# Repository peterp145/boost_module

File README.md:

# boost_module
op amp boost module for guitar. designed for use on a breadboard or in an enclosure.

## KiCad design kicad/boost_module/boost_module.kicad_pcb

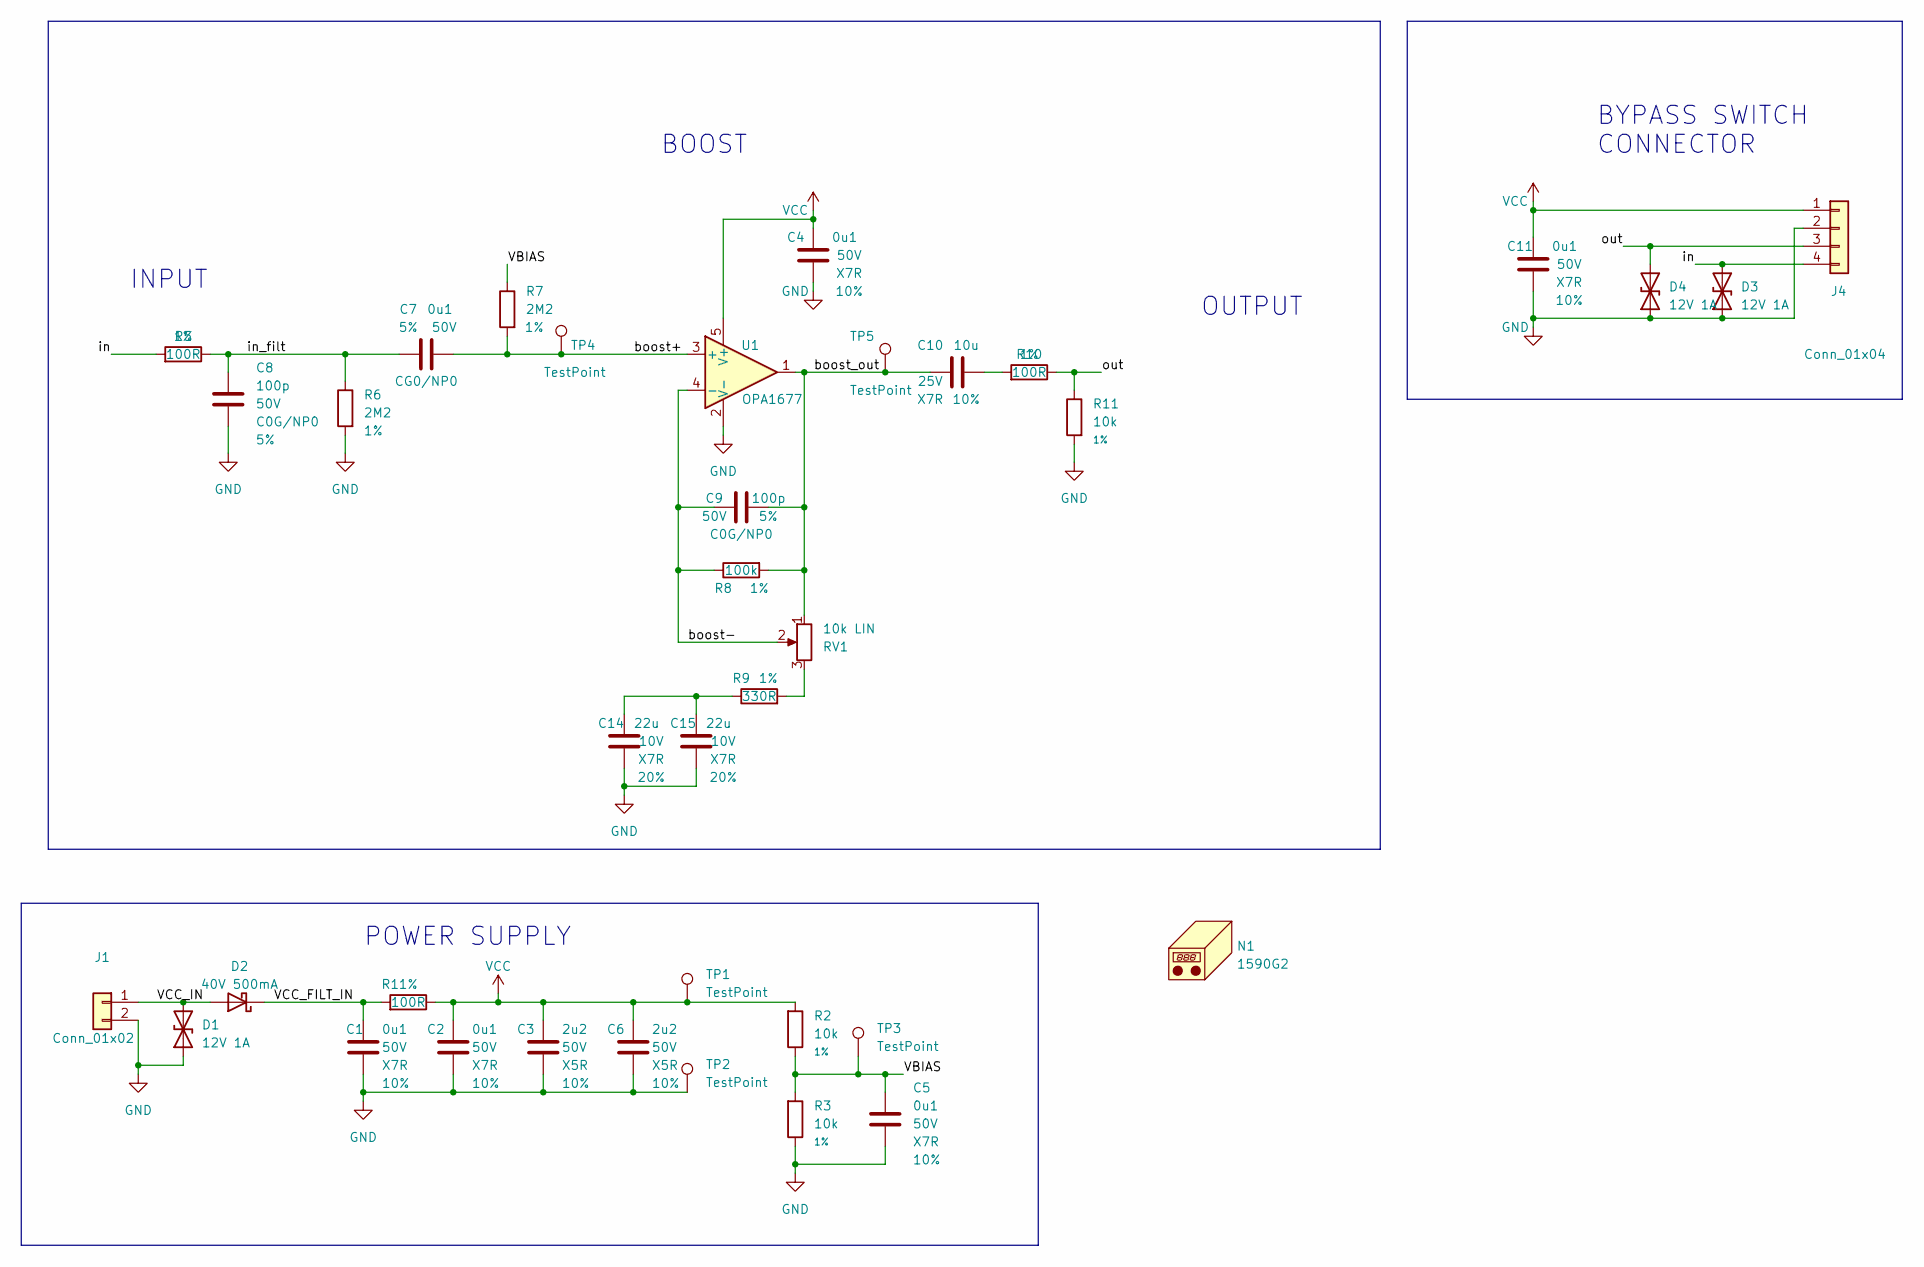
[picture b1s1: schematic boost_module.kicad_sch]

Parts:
C1, C2, C4, C5, C11: 0u1; C_0603_1608Metric; Voltage 50V; Tolerance 10%; MPN1 CL10B104KB8NNWC
C3, C6: 2u2; C_0603_1608Metric; Voltage 50V; Tolerance 10%; MPN1 UMK107BBJ225KA-T
C7: 0u1; C_1206_3216Metric; Voltage 50V; Tolerance 5%; MPN1 CGA5L2C0G1H104J160AA
C8, C9: 100p; C_0603_1608Metric; Voltage 50V; Tolerance 5%; MPN1 CC0603JRNPO9BN101
C10: 10u; C_1206_3216Metric; Voltage 25V; Tolerance 10%; MPN1 CL31B106KAHNNNE
C14, C15: 22u; C_1206_3216Metric; Voltage 10V; Tolerance 20%; mfg_pn CL32B226MOJNNNE
D1, D3, D4: 12V 1A; D_SOD-323; MPN1 PJGBLC12C_R1_00001
D2: 40V 500mA; D_SOD-323; MPN1 CMDSH05-4 TR PBFREE
J1: Conn_01x02; PinHeader_1x02_P2.54mm_Vertical
J4: Conn_01x04; PinSocket_1x04_P2.54mm_Vertical
N1: 1590G2; 1590G
R1, R5, R10: 100R; R_0603_1608Metric; Tolerance 1%; MPN1 RC0603FR-07100RL
R2, R3, R11: 10k; R_0603_1608Metric; Tolerance 1%; MPN1 RC0603FR-0710KL
R6, R7: 2M2; R_0603_1608Metric; Tolerance 1%; MPN1 RC0603FR-072M2L
R8: 100k; R_0603_1608Metric; Tolerance 1%; MPN1 RC0603FR-07100KL
R9: 330R; R_0603_1608Metric; Tolerance 1%; MPN1 RC0603FR-07330RL
RV1: 10k LIN; Pot_RD901F-40-00D_Single_Vertical; Tolerance xx%
TP1, TP2, TP3, TP4, TP5: TestPoint; TestPoint_Pad_D1.0mm
U1: OPA1677; TSOT-23-5; MPN1 OPA1677DBVR

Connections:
/VBIAS: C5.1, R2.2, R3.1, R7.2, TP3.1
/VCC_FILT_IN: C1.1, D2.1 (K), R1.1
/VCC_IN: D1.2 (A2), D2.2 (A), J1.1
/boost+: C7.2, R7.1, TP4.1, U1.3 (+)
/boost-: C9.1, R8.2, RV1.2, U1.4 (-)
/boost_out: C9.2, C10.1, R8.1, RV1.1, TP5.1, U1.1
/in: D3.2 (A2), J4.4, R5.1
/in_filt: C7.1, C8.2, R5.2, R6.2
/out: D4.2 (A2), J4.3, R10.2, R11.2
GND: C1.2, C2.2, C3.2, C4.2, C5.2, C6.2, C8.1, C11.2, C14.2, C15.2, D1.1 (A1), D3.1 (A1), D4.1 (A1), J1.2, J4.2, R3.2, R6.1, R11.1, TP2.1, U1.2 (V-)
unnamed: C10.2, R10.1
unnamed: C14.1, C15.1, R9.2
unnamed: R9.1, RV1.3
VCC: C2.1, C3.1, C4.1, C6.1, C11.1, J4.1, R1.2, R2.1, TP1.1, U1.5 (V+)

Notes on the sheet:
BYPASS SWITCH CONNECTOR
OUTPUT
INPUT
BOOST
POWER SUPPLY

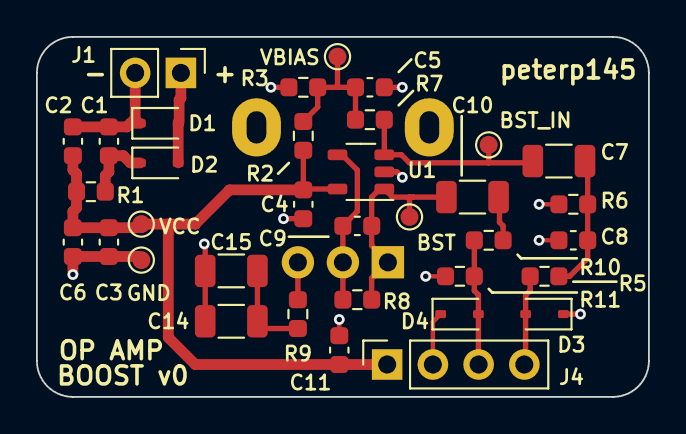
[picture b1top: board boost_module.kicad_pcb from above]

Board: 2 copper layers, 34.0 x 20.0 mm, 37 parts (1 on the bottom side), 14 nets.

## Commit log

2023-01-21 schematic entry
2023-01-21 footprint assignment
2023-01-21 initial placement
2023-01-31 component selection
2023-02-01 added 1590G2 enclosure footprint
2023-02-03 changed layout for 1591XXLTBU enclosure
2023-02-09 placement and routing
2023-02-18 rev 0 export for manufacture
